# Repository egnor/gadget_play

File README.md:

# gadget_play
Experimental gadgets and gizmos

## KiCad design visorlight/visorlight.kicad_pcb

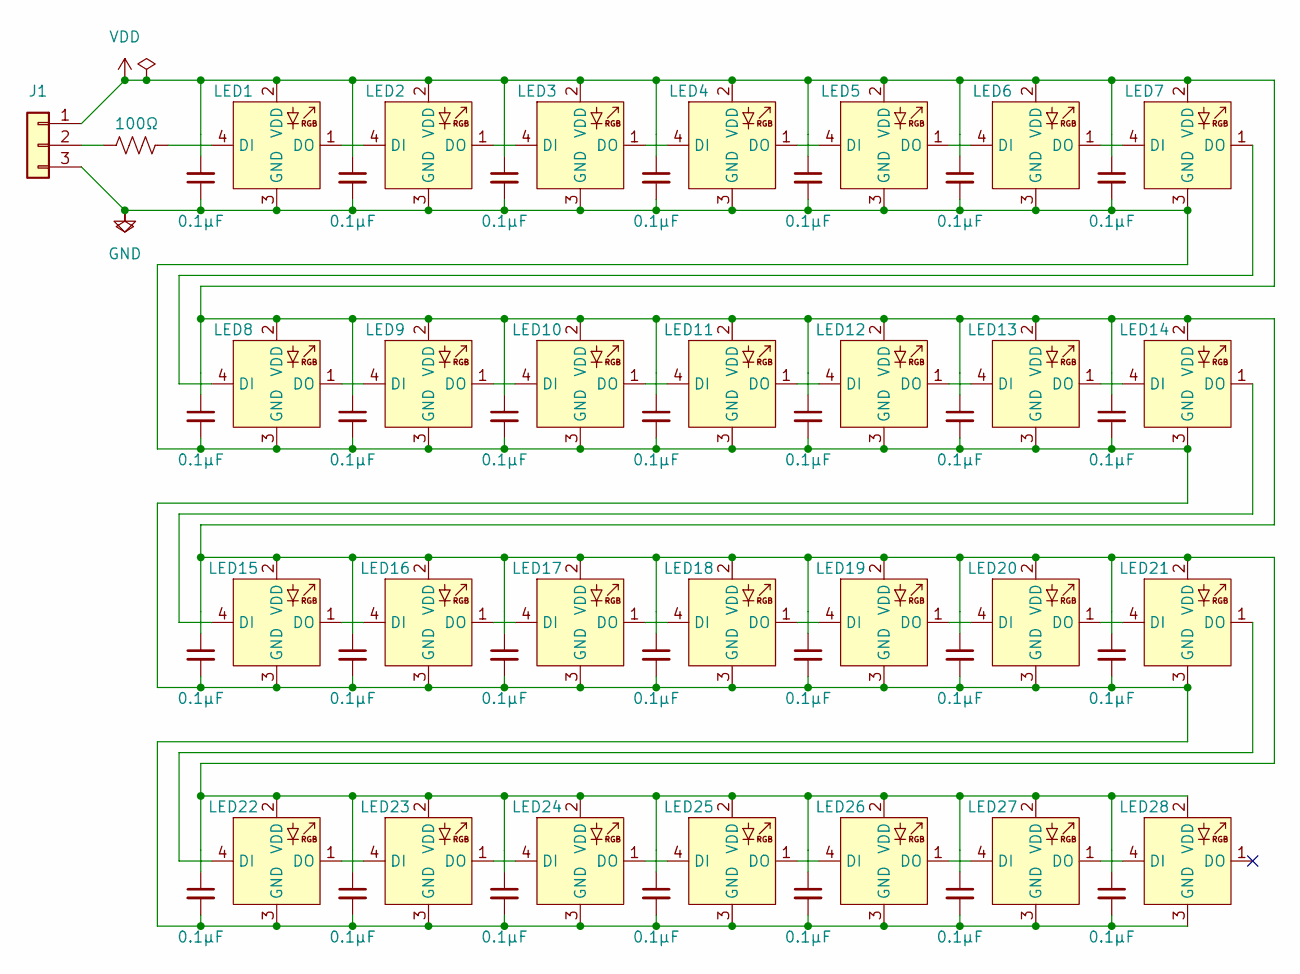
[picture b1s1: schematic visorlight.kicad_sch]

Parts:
C1, C2, C3, C4, C5, C6, C7, C8, C9, C10, C11, C12, C13, C14, C15, C16, C17, C18, C19, C20, C21, C22, C23, C24, C25, C26, C27, C28: 0.1µF; C_0603_1608Metric; LCSC# C14663
J1: Conn_01x03; Wires_3x_Relief
LED1, LED2, LED3, LED4, LED5, LED6, LED7, LED8, LED9, LED10, LED11, LED12, LED13, LED14, LED15, LED16, LED17, LED18, LED19, LED20, LED21, LED22, LED23, LED24, LED25, LED26, LED27, LED28: LED_1010RGBC; LCSC# C5349953
R1: 100Ω; R_0402_1005Metric; LCSC# C25076

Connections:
GND: C1.1, C2.2, C3.2, C4.2, C5.2, C6.2, C7.2, C8.2, C9.2, C10.2, C11.2, C12.2, C13.2, C14.2, C15.2, C16.2, C17.2, C18.2, C19.2, C20.2, C21.2, C22.2, C23.2, C24.2, C25.2, C26.2, C27.2, C28.2, J1.3, LED1.3 (GND), LED2.3 (GND), LED3.3 (GND), LED4.3 (GND), LED5.3 (GND), LED6.3 (GND), LED7.3 (GND), LED8.3 (GND), LED9.3 (GND), LED10.3 (GND), LED11.3 (GND), LED12.3 (GND), LED13.3 (GND), LED14.3 (GND), LED15.3 (GND), LED16.3 (GND), LED17.3 (GND), LED18.3 (GND), LED19.3 (GND), LED20.3 (GND), LED21.3 (GND), LED22.3 (GND), LED23.3 (GND), LED24.3 (GND), LED25.3 (GND), LED26.3 (GND), LED27.3 (GND), LED28.3 (GND)
unnamed: J1.2, R1.2
unnamed: LED1.4 (DI), R1.1
unnamed: LED1.1 (DO), LED2.4 (DI)
unnamed: LED2.1 (DO), LED3.4 (DI)
unnamed: LED3.1 (DO), LED4.4 (DI)
unnamed: LED4.1 (DO), LED5.4 (DI)
unnamed: LED5.1 (DO), LED6.4 (DI)
unnamed: LED6.1 (DO), LED7.4 (DI)
unnamed: LED7.1 (DO), LED8.4 (DI)
unnamed: LED8.1 (DO), LED9.4 (DI)
unnamed: LED9.1 (DO), LED10.4 (DI)
unnamed: LED10.1 (DO), LED11.4 (DI)
unnamed: LED11.1 (DO), LED12.4 (DI)
unnamed: LED12.1 (DO), LED13.4 (DI)
unnamed: LED13.1 (DO), LED14.4 (DI)
unnamed: LED14.1 (DO), LED15.4 (DI)
unnamed: LED15.1 (DO), LED16.4 (DI)
unnamed: LED16.1 (DO), LED17.4 (DI)
unnamed: LED17.1 (DO), LED18.4 (DI)
unnamed: LED18.1 (DO), LED19.4 (DI)
unnamed: LED19.1 (DO), LED20.4 (DI)
unnamed: LED20.1 (DO), LED21.4 (DI)
unnamed: LED21.1 (DO), LED22.4 (DI)
unnamed: LED22.1 (DO), LED23.4 (DI)
unnamed: LED23.1 (DO), LED24.4 (DI)
unnamed: LED24.1 (DO), LED25.4 (DI)
unnamed: LED25.1 (DO), LED26.4 (DI)
unnamed: LED26.1 (DO), LED27.4 (DI)
unnamed: LED27.1 (DO), LED28.4 (DI)
VDD: C1.2, C2.1, C3.1, C4.1, C5.1, C6.1, C7.1, C8.1, C9.1, C10.1, C11.1, C12.1, C13.1, C14.1, C15.1, C16.1, C17.1, C18.1, C19.1, C20.1, C21.1, C22.1, C23.1, C24.1, C25.1, C26.1, C27.1, C28.1, J1.1, LED1.2 (VDD), LED2.2 (VDD), LED3.2 (VDD), LED4.2 (VDD), LED5.2 (VDD), LED6.2 (VDD), LED7.2 (VDD), LED8.2 (VDD), LED9.2 (VDD), LED10.2 (VDD), LED11.2 (VDD), LED12.2 (VDD), LED13.2 (VDD), LED14.2 (VDD), LED15.2 (VDD), LED16.2 (VDD), LED17.2 (VDD), LED18.2 (VDD), LED19.2 (VDD), LED20.2 (VDD), LED21.2 (VDD), LED22.2 (VDD), LED23.2 (VDD), LED24.2 (VDD), LED25.2 (VDD), LED26.2 (VDD), LED27.2 (VDD), LED28.2 (VDD)

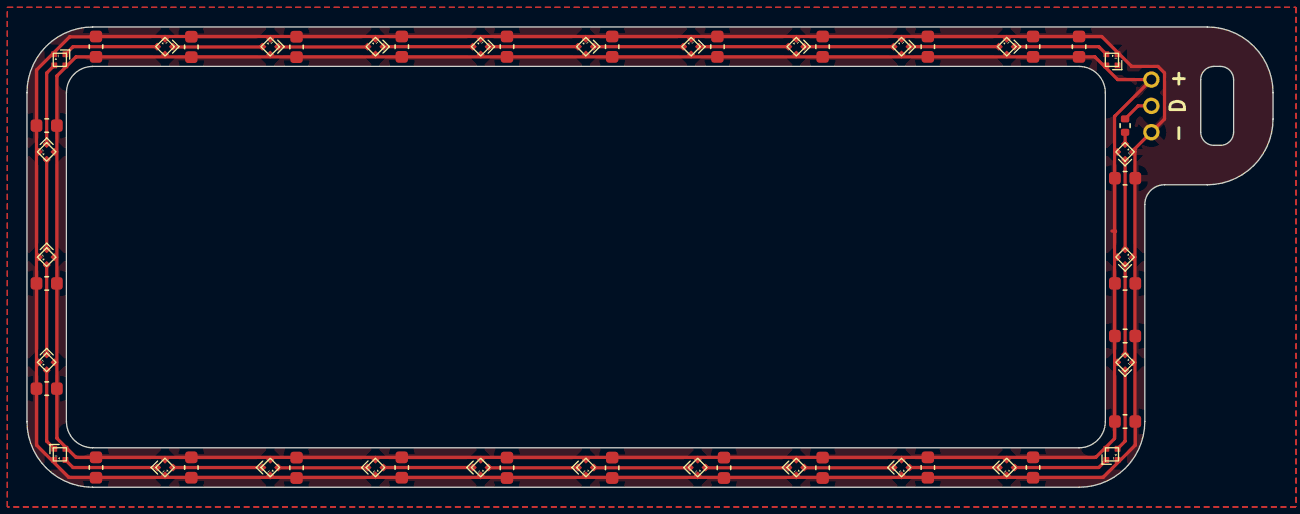
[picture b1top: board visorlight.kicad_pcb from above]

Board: 2 copper layers, 94.8 x 35.0 mm, 58 parts (0 on the bottom side), 31 nets.

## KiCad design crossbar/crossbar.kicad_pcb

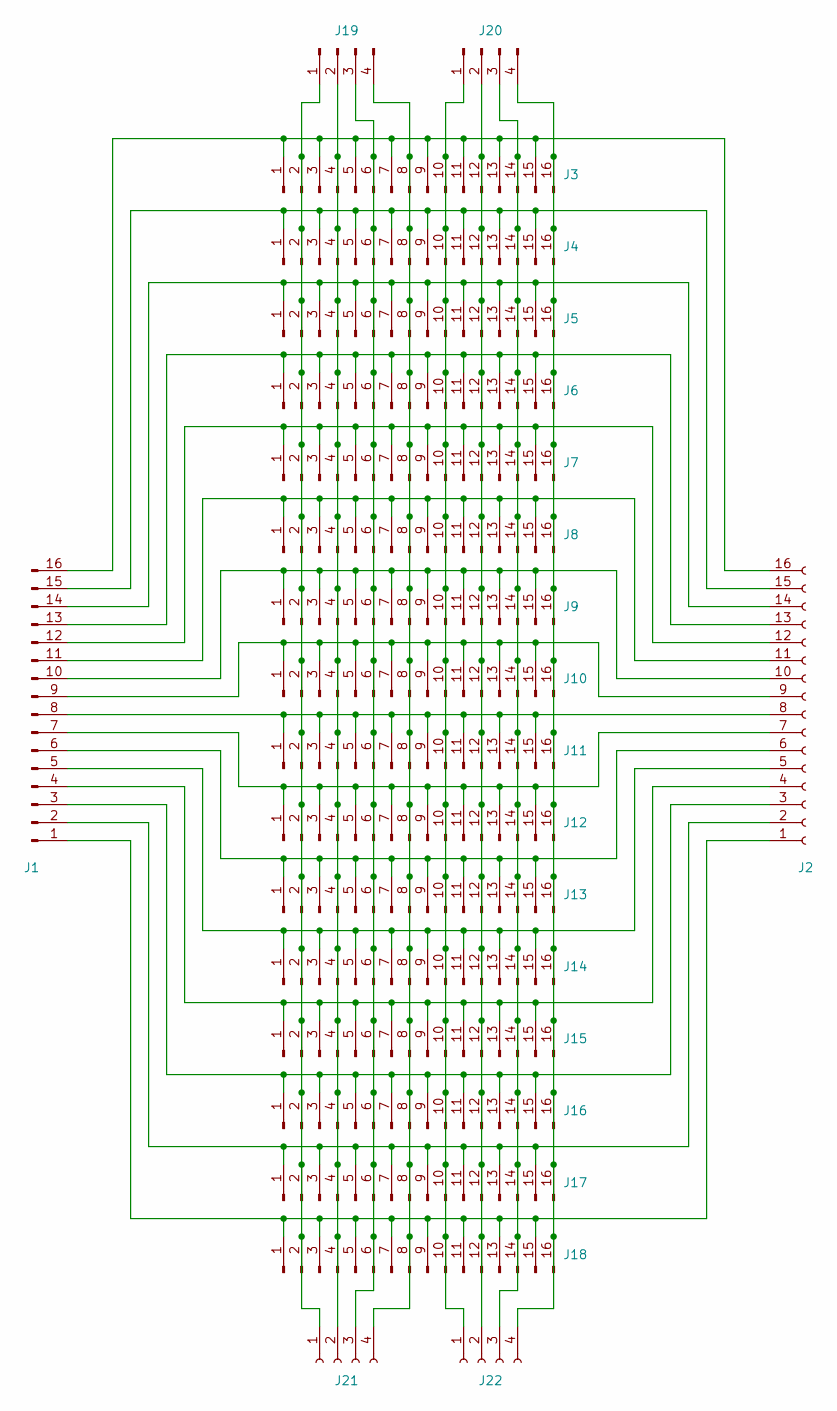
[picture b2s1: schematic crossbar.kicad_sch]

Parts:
J1: Conn_01x16_Pin; PinHeader_1x16_P2.54mm_Horizontal; LCSC# C2894958
J2: Conn_01x16_Socket; PinSocket_1x16_P2.54mm_Horizontal; LCSC# C2897398
J3, J4, J5, J6, J7, J8, J9, J10, J11, J12, J13, J14, J15, J16, J17, J18: Conn_01x16_Pin; PinHeader_1x16_P2.54mm_Vertical; LCSC# C2894939
J19, J20: Conn_01x04_Pin; PinHeader_1x04_P2.54mm_Horizontal; LCSC# C2894946
J21, J22: Conn_01x04_Socket; PinSocket_1x04_P2.54mm_Horizontal; LCSC# C2897386

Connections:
unnamed: J1.1, J2.1, J18.1, J18.3, J18.5, J18.7, J18.9, J18.11, J18.13, J18.15
unnamed: J1.2, J2.2, J17.1, J17.3, J17.5, J17.7, J17.9, J17.11, J17.13, J17.15
unnamed: J1.3, J2.3, J16.1, J16.3, J16.5, J16.7, J16.9, J16.11, J16.13, J16.15
unnamed: J1.4, J2.4, J15.1, J15.3, J15.5, J15.7, J15.9, J15.11, J15.13, J15.15
unnamed: J1.5, J2.5, J14.1, J14.3, J14.5, J14.7, J14.9, J14.11, J14.13, J14.15
unnamed: J1.6, J2.6, J13.1, J13.3, J13.5, J13.7, J13.9, J13.11, J13.13, J13.15
unnamed: J1.7, J2.7, J12.1, J12.3, J12.5, J12.7, J12.9, J12.11, J12.13, J12.15
unnamed: J1.8, J2.8, J11.1, J11.3, J11.5, J11.7, J11.9, J11.11, J11.13, J11.15
unnamed: J1.9, J2.9, J10.1, J10.3, J10.5, J10.7, J10.9, J10.11, J10.13, J10.15
unnamed: J1.10, J2.10, J9.1, J9.3, J9.5, J9.7, J9.9, J9.11, J9.13, J9.15
unnamed: J1.11, J2.11, J8.1, J8.3, J8.5, J8.7, J8.9, J8.11, J8.13, J8.15
unnamed: J1.12, J2.12, J7.1, J7.3, J7.5, J7.7, J7.9, J7.11, J7.13, J7.15
unnamed: J1.13, J2.13, J6.1, J6.3, J6.5, J6.7, J6.9, J6.11, J6.13, J6.15
unnamed: J1.14, J2.14, J5.1, J5.3, J5.5, J5.7, J5.9, J5.11, J5.13, J5.15
unnamed: J1.15, J2.15, J4.1, J4.3, J4.5, J4.7, J4.9, J4.11, J4.13, J4.15
unnamed: J1.16, J2.16, J3.1, J3.3, J3.5, J3.7, J3.9, J3.11, J3.13, J3.15
unnamed: J3.2, J4.2, J5.2, J6.2, J7.2, J8.2, J9.2, J10.2, J11.2, J12.2, J13.2, J14.2, J15.2, J16.2, J17.2, J18.2, J19.1, J21.1
unnamed: J3.4, J4.4, J5.4, J6.4, J7.4, J8.4, J9.4, J10.4, J11.4, J12.4, J13.4, J14.4, J15.4, J16.4, J17.4, J18.4, J19.2, J21.2
unnamed: J3.6, J4.6, J5.6, J6.6, J7.6, J8.6, J9.6, J10.6, J11.6, J12.6, J13.6, J14.6, J15.6, J16.6, J17.6, J18.6, J19.3, J21.3
unnamed: J3.8, J4.8, J5.8, J6.8, J7.8, J8.8, J9.8, J10.8, J11.8, J12.8, J13.8, J14.8, J15.8, J16.8, J17.8, J18.8, J19.4, J21.4
unnamed: J3.10, J4.10, J5.10, J6.10, J7.10, J8.10, J9.10, J10.10, J11.10, J12.10, J13.10, J14.10, J15.10, J16.10, J17.10, J18.10, J20.1, J22.1
unnamed: J3.12, J4.12, J5.12, J6.12, J7.12, J8.12, J9.12, J10.12, J11.12, J12.12, J13.12, J14.12, J15.12, J16.12, J17.12, J18.12, J20.2, J22.2
unnamed: J3.14, J4.14, J5.14, J6.14, J7.14, J8.14, J9.14, J10.14, J11.14, J12.14, J13.14, J14.14, J15.14, J16.14, J17.14, J18.14, J20.3, J22.3
unnamed: J3.16, J4.16, J5.16, J6.16, J7.16, J8.16, J9.16, J10.16, J11.16, J12.16, J13.16, J14.16, J15.16, J16.16, J17.16, J18.16, J20.4, J22.4

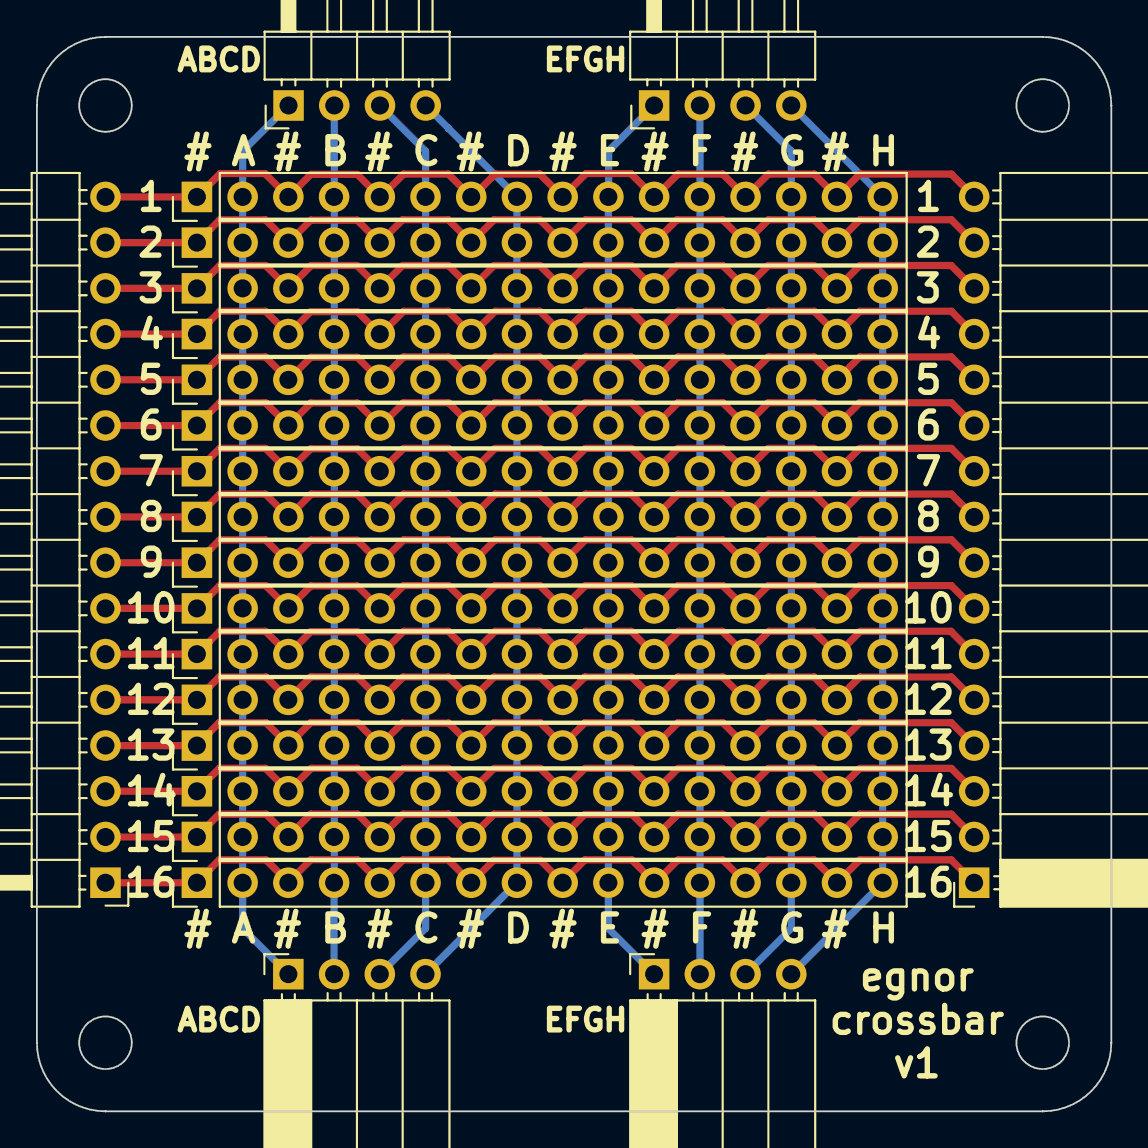
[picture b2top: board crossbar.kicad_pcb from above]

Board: 2 copper layers, 59.7 x 59.7 mm, 22 parts (0 on the bottom side), 24 nets.

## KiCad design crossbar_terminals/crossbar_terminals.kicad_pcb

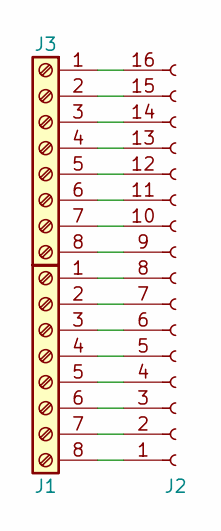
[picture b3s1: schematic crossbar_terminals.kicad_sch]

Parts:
J1, J3: Screw_Terminal_01x08; TerminalBlock_Phoenix_MPT-0,5-8-2.54_1x08_P2.54mm_Horizontal; LCSC# C5188448
J2: Conn_01x16_Socket; PinSocket_1x16_P2.54mm_Horizontal; LCSC# C2897398

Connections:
unnamed: J1.1, J2.8
unnamed: J1.2, J2.7
unnamed: J1.3, J2.6
unnamed: J1.4, J2.5
unnamed: J1.5, J2.4
unnamed: J1.6, J2.3
unnamed: J1.7, J2.2
unnamed: J1.8, J2.1
unnamed: J2.9, J3.8
unnamed: J2.10, J3.7
unnamed: J2.11, J3.6
unnamed: J2.12, J3.5
unnamed: J2.13, J3.4
unnamed: J2.14, J3.3
unnamed: J2.15, J3.2
unnamed: J2.16, J3.1

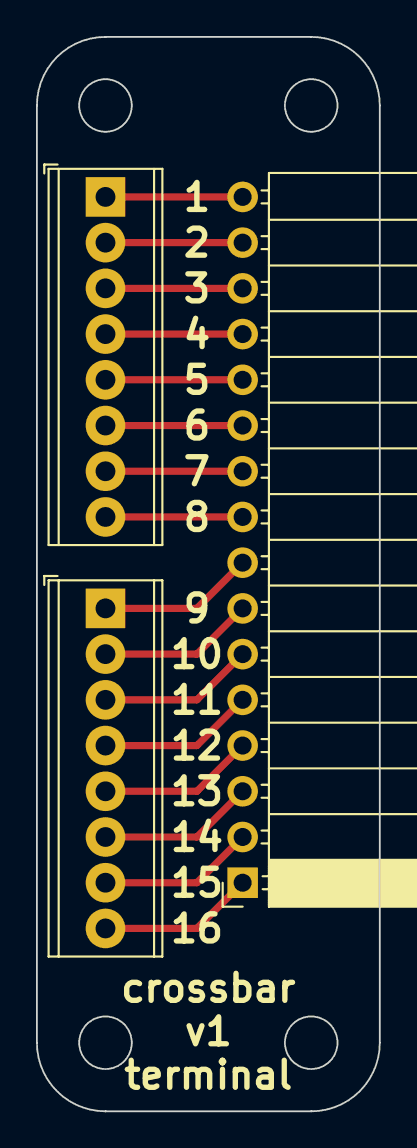
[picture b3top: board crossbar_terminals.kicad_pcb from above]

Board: 2 copper layers, 19.1 x 59.7 mm, 3 parts (0 on the bottom side), 16 nets.

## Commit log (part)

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2021-07-25 start flexmatrix exploration
2021-07-26 pretty lights
2021-07-30 new minimal ardi file, svg layout, more puttering
2021-07-31 tune touch detection
2021-08-24 nametag hacking play
2021-08-28 more nametag updates
2021-08-28 include downloaded apks
2021-08-28 more updates to tools
2021-08-28 fix send hex
2021-08-29 rename capture files, add a glyphs file
2021-08-29 tools update
2021-08-29 actual module code
2021-08-29 oops cache
2021-08-29 ignore python cache
2021-08-29 remove packets files no longer needed
2021-08-29 more updates, more expected value checking
2021-08-30 more updates to nametag stuffs
2021-08-31 new capture!
2021-08-31 add extracted json file from app for reference
2021-09-01 rearrange files, support animations
2021-09-01 various updates
2021-09-01 fixes for python 3.7, some asset renames
2021-09-01 nametag was split into a separate repo
2022-05-12 add some test code for the UWB dev kits
2022-05-14 better SPI interface
2022-05-14 fix reset
2022-05-15 rename, more registers
2022-05-16 avoid specific python dependency
2022-05-17 add picam, reorganize env dirs
2022-05-17 fix build
2022-05-17 C++ camera test
2022-05-17 consolidate gitignore
2022-05-17 rename
2022-05-18 remove obsolete Pipfiles
2022-05-18 picap test app that can save images!
2022-05-18 manual exposure overrides
2022-05-19 start color_test
2022-05-21 better color tracking and diagnostics, code refactor
2022-05-21 improve debugging images
2022-05-21 better color sensing
2022-05-24 simple test for mercury python API
2022-05-27 color sensor code
2022-05-28 fix bug in rgb output, improve output consistency
2022-05-28 fix degree alignment
2022-06-01 adapt to Metro M4
2022-06-01 more registers
2022-06-01 KiCad design for color carrier
2022-06-01 refactor into driver
2022-06-02 packet transmit!
2022-06-02 tighten up the lead time on TX
2022-06-02 migrate color to pg repo
2022-06-03 more fixes to transmit handling, error messages
2022-06-03 receive???
2022-06-04 more fussing...
2022-06-04 squirrel away vendor zip
2022-06-05 unpack decadriver for convenience
2022-06-05 add examples for quick references
2022-06-05 add some registers from Qorvo driver
2022-06-05 more tweaks inspired by deca_driver
2022-06-06 move common code to library
2022-06-10 various fixes
2022-06-10 start migrating to platformio
2022-06-10 clean up some renames
2022-06-10 finish up platformio migration
2022-06-10 give a bit more time to the transmit
2022-06-10 add DWM3000 carrier mini board
2022-06-26 put python_venv in the top level
2022-06-26 oops flip
2023-08-24 first draft crossbar board
2023-08-24 crossbar & terminals
2024-01-04 visorlight
2024-01-04 ignore bak
2024-01-23 moar leds
2024-02-02 tinyblink start
2024-03-27 rp2040
2024-03-27 tweak
2024-05-05 pixelfont play
2024-05-05 unzoom
2024-05-06 proofy goodness
2024-05-07 proofy
2024-05-10 trivial
2024-05-17 font
2024-05-26 clean up some stuff
2024-05-26 move pintest here
2024-05-27 add index
2024-05-27 add URL
2024-05-27 egnor
2024-05-27 hmmmm
2024-05-27 update sum
2024-05-27 version bump
2024-05-27 oops
2024-05-28 remove tinyblink, pintest does it better
2024-05-28 get rid of that nonsense
2024-05-28 more sketchy business
2024-05-28 more tests
2024-06-02 re enable LED strip control
2024-06-15 stuff
2024-06-15 neopixelbus
2024-06-27 qualia
2024-07-06 11px black
2024-07-17 switch to Adafruit to avoid legacy RMT issue
2024-07-18 13px bold
2024-07-20 ESP32-S2 support
2024-07-23 pins
2024-08-11 add bug case
2024-09-20 upgrade?
2024-09-20 pintest improvements
2024-09-20 add orange
2024-09-24 add esp32, add pullup, etc
2024-10-24 fixes
2024-10-24 flush input
2025-07-28 RP2040-RFM support
2025-12-09 remove ok_logging_test
